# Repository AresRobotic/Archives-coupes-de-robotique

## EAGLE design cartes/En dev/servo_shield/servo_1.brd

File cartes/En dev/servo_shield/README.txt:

* Vérifier connecteur AX-12
Attendre de réussir à faire fonctionner les AX12 pour l'envoyer

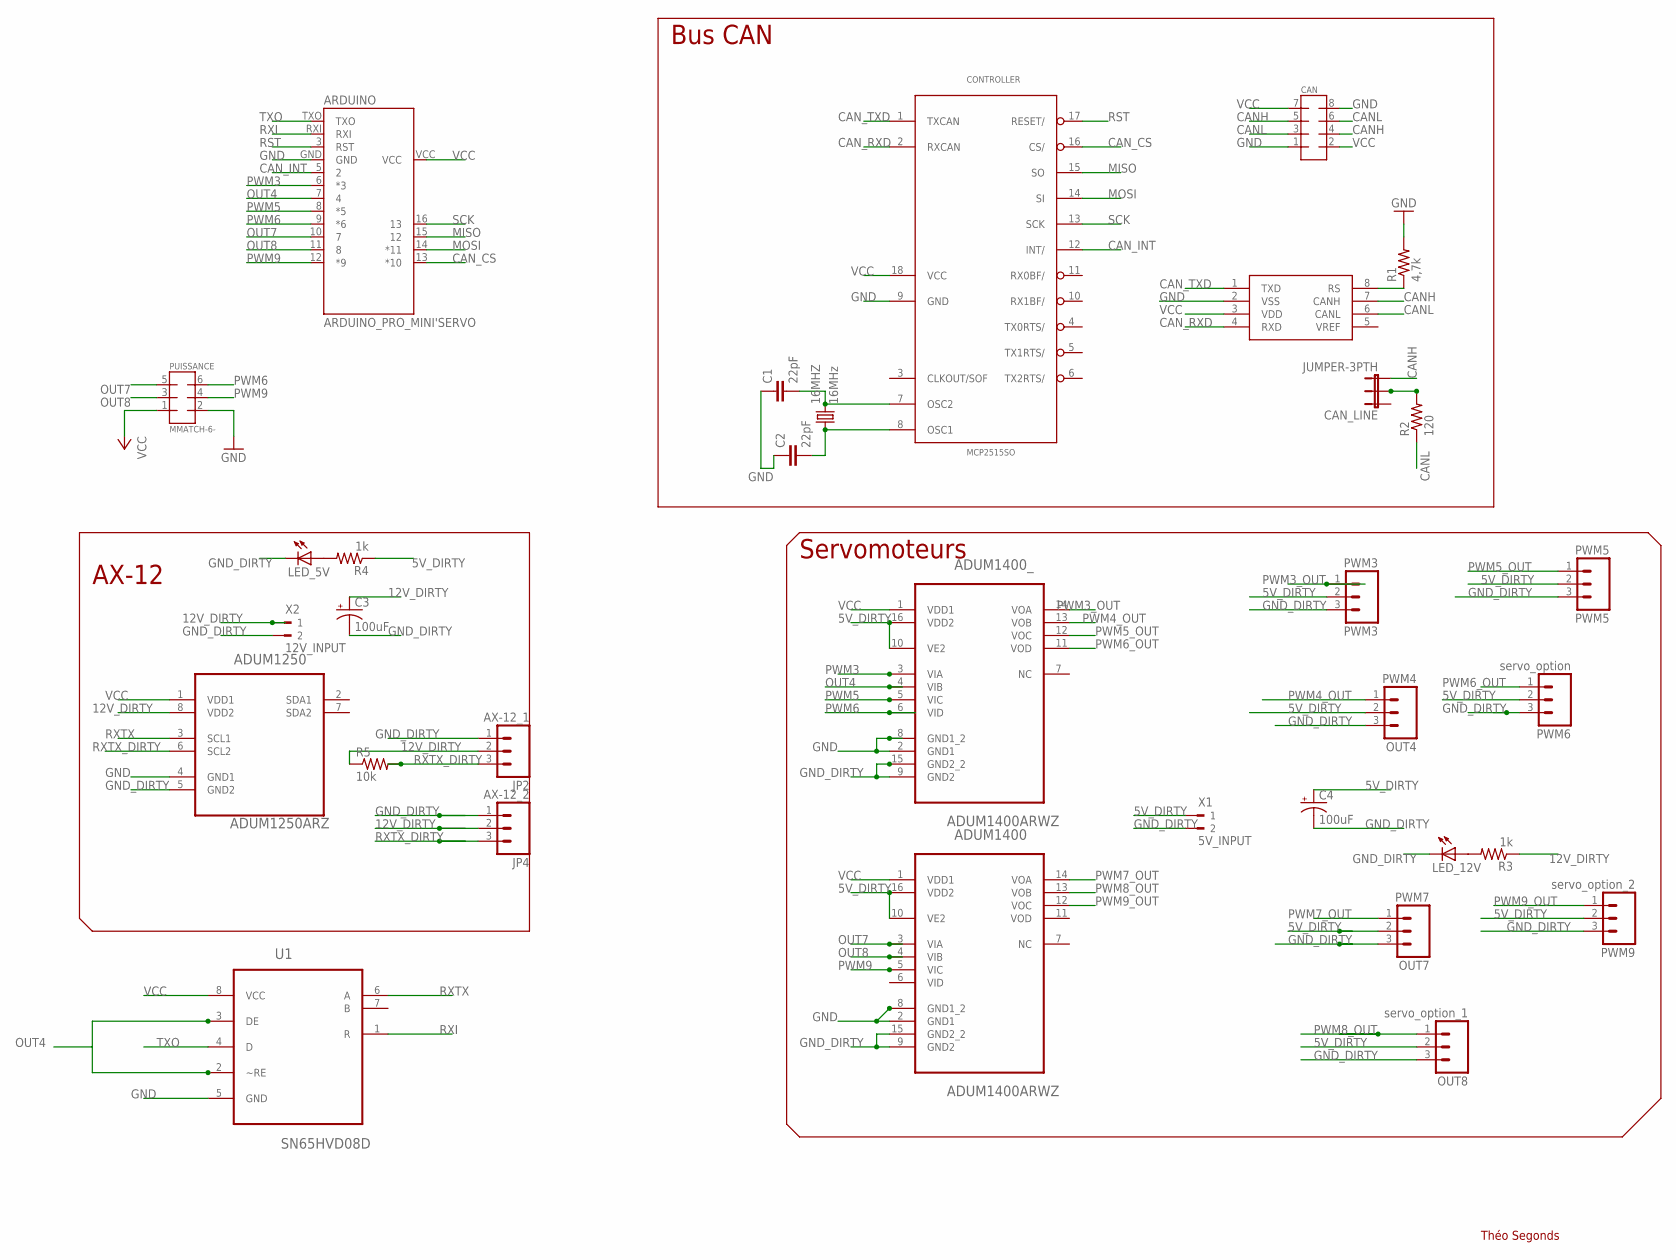
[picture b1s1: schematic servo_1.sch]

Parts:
16MHZ: 16MHz; HC49/S; MPN HC49SM-3.6864-30-50-60-16-ATF
ADUM1250: ADUM1250ARZ; SOIC127P600X175-8N
ADUM1400, ADUM1400_: ADUM1400ARWZ; SOIC127P1032X265-16N
ARDUINO: ARDUINO_PRO_MINI'SERVO; ARDUINO_PRO_MINI
C1, C2: 22pF; 0805; MPN 08055A220JAT2A
C3, C4: 100uF; CPOL-RADIAL-100UF-25V; MPN 100TXW100MEFC8X30
CAN: MMATCH-8-PTH; AMP-215079-8
CAN_LINE: JUMPER-3PTH; 1X03
CONTROLLER: MCP2515SO; SO18L
JP2: AX-12_1; MOLEX-1X3
JP4: AX-12_2; MOLEX-1X3
LED_5V, LED_12V: LEDCHIPLED_0805; CHIPLED_0805
OUT4: PWM4; 1X03
OUT7: PWM7; 1X03
OUT8: servo_option_1; 1X03
PUISSANCE: MMATCH-6-; AMP-215079-6
PWM3: PWM3; 1X03
PWM5: PWM5; 1X03
PWM6: servo_option; 1X03
PWM9: servo_option_2; 1X03
R1: 4,7k; 0805
R2: 120; 0805
R3, R4: 1k; 0805
R5: 10k; 0805
TRANSCEIVER: MCP2551; SO08; MPN MCP2551-I/SN...
U1: SN65HVD08D; SOIC127P600X175-8N
X1: 5V_INPUT; 90-2
X2: 12V_INPUT; 90-2

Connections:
5V_DIRTY: ADUM1400.10 (VE2), ADUM1400.16 (VDD2), ADUM1400_.10 (VE2), ADUM1400_.16 (VDD2), C4.1 (+), OUT4.2, OUT7.2, OUT8.2, PWM3.2, PWM5.2, PWM6.2, PWM9.2, R4.1, X1.1
12V_DIRTY: ADUM1250.8 (VDD2), C3.1 (+), JP2.2, JP4.2, R3.1, R5.1, X2.1
CANH: CAN.4, CAN.5, CAN_LINE.3, TRANSCEIVER.7 (CANH)
CANL: CAN.3, CAN.6, R2.1, TRANSCEIVER.6 (CANL)
CAN_CS: ARDUINO.13 (*10), CONTROLLER.16 (CS/)
CAN_INT: ARDUINO.5 (2), CONTROLLER.12 (INT/)
CAN_RXD: CONTROLLER.2 (RXCAN), TRANSCEIVER.4 (RXD)
CAN_TXD: CONTROLLER.1 (TXCAN), TRANSCEIVER.1 (TXD)
GND: ADUM1250.4 (GND1), ADUM1400.2 (GND1), ADUM1400.8 (GND1_2), ADUM1400_.2 (GND1), ADUM1400_.8 (GND1_2), ARDUINO.GND, C1.1, C2.1, CAN.1, CAN.8, CONTROLLER.9 (GND), PUISSANCE.2 (4), R1.2, TRANSCEIVER.2 (VSS), U1.5 (GND)
GND_DIRTY: ADUM1250.5 (GND2), ADUM1400.9 (GND2), ADUM1400.15 (GND2_2), ADUM1400_.9 (GND2), ADUM1400_.15 (GND2_2), C3.2 (-), C4.2 (-), JP2.1, JP4.1, LED_5V.C, LED_12V.C, OUT4.3, OUT7.3, OUT8.3, PWM3.3, PWM5.3, PWM6.3, PWM9.3, X1.2, X2.2
MISO: ARDUINO.15 (12), CONTROLLER.15 (SO)
MOSI: ARDUINO.14 (*11), CONTROLLER.14 (SI)
unnamed: 16MHZ.2, C1.2, CONTROLLER.7 (OSC2)
unnamed: 16MHZ.1, C2.2, CONTROLLER.8 (OSC1)
unnamed: LED_12V.A, R3.2
unnamed: R1.1, TRANSCEIVER.8 (RS)
unnamed: LED_5V.A, R4.2
unnamed: CAN_LINE.2, R2.2
OUT4: ADUM1400_.4 (VIB), ARDUINO.7 (4), U1.2 (~RE), U1.3 (DE)
OUT7: ADUM1400.3 (VIA), ARDUINO.10 (7), PUISSANCE.5 (7)
OUT8: ADUM1400.4 (VIB), ARDUINO.11 (8), PUISSANCE.3 (5)
PWM3: ADUM1400_.3 (VIA), ARDUINO.6 (*3)
PWM3_OUT: ADUM1400_.14 (VOA), PWM3.1
PWM4_OUT: ADUM1400_.13 (VOB), OUT4.1
PWM5: ADUM1400_.5 (VIC), ARDUINO.8 (*5)
PWM5_OUT: ADUM1400_.12 (VOC), PWM5.1
PWM6: ADUM1400_.6 (VID), ARDUINO.9 (*6), PUISSANCE.6 (8)
PWM6_OUT: ADUM1400_.11 (VOD), PWM6.1
PWM7_OUT: ADUM1400.14 (VOA), OUT7.1
PWM8_OUT: ADUM1400.13 (VOB), OUT8.1
PWM9: ADUM1400.5 (VIC), ARDUINO.12 (*9), PUISSANCE.4 (6)
PWM9_OUT: ADUM1400.12 (VOC), PWM9.1
RST: ARDUINO.3 (RST), CONTROLLER.17 (RESET/)
RXI: ARDUINO.RXI, U1.1 (R)
RXTX: ADUM1250.3 (SCL1), U1.6 (A)
RXTX_DIRTY: ADUM1250.6 (SCL2), JP2.3, JP4.3, R5.2
SCK: ARDUINO.16 (13), CONTROLLER.13 (SCK)
TXO: ARDUINO.TXO, U1.4 (D)
VCC: ADUM1250.1 (VDD1), ADUM1400.1 (VDD1), ADUM1400_.1 (VDD1), ARDUINO.VCC, CAN.2, CAN.7, CONTROLLER.18 (VCC), PUISSANCE.1 (3), TRANSCEIVER.3 (VDD), U1.8 (VCC)

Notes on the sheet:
Bus CAN
AX-12
Servomoteurs
Théo Segonds

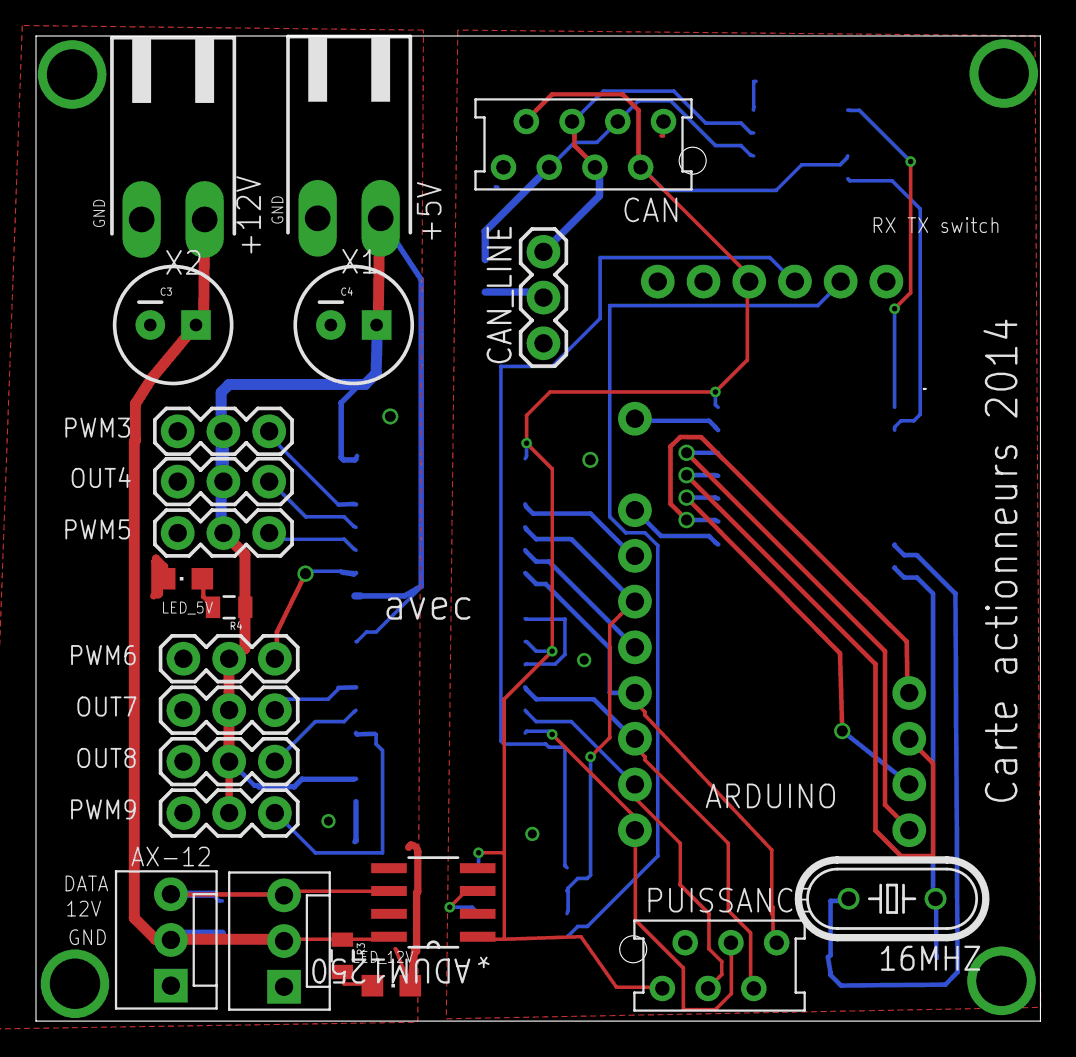
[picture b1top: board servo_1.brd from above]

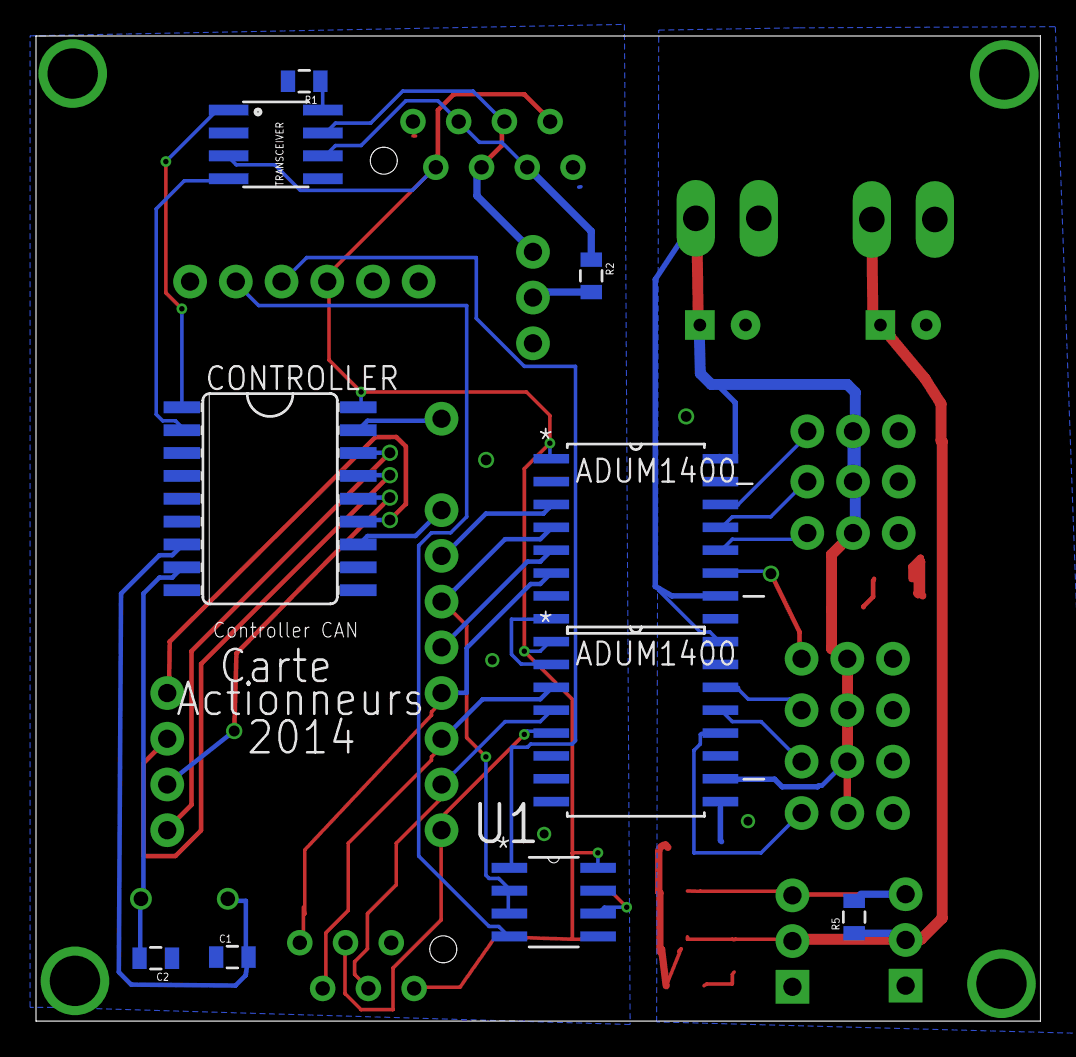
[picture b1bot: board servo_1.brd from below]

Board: 2 copper layers, 55.8 x 54.7 mm, 33 parts (10 on the bottom side), 39 nets.

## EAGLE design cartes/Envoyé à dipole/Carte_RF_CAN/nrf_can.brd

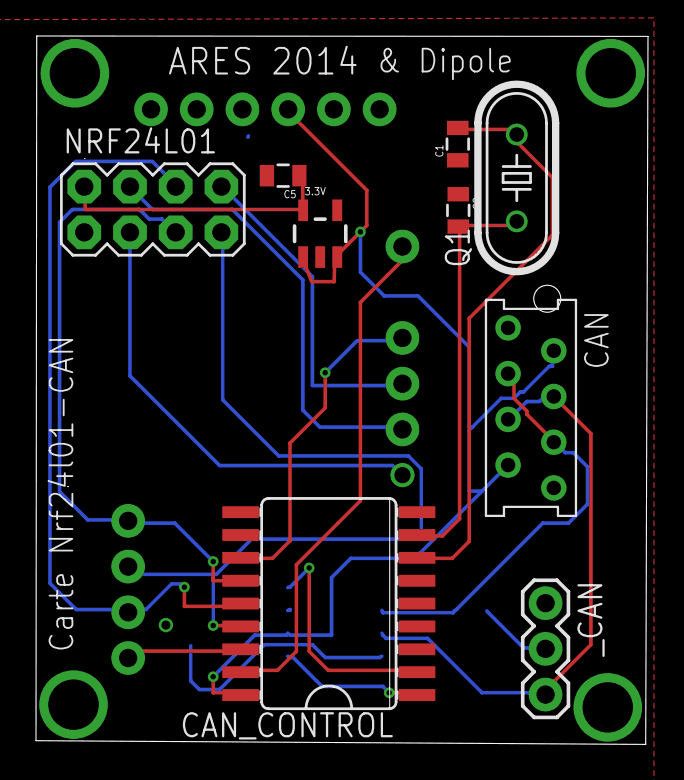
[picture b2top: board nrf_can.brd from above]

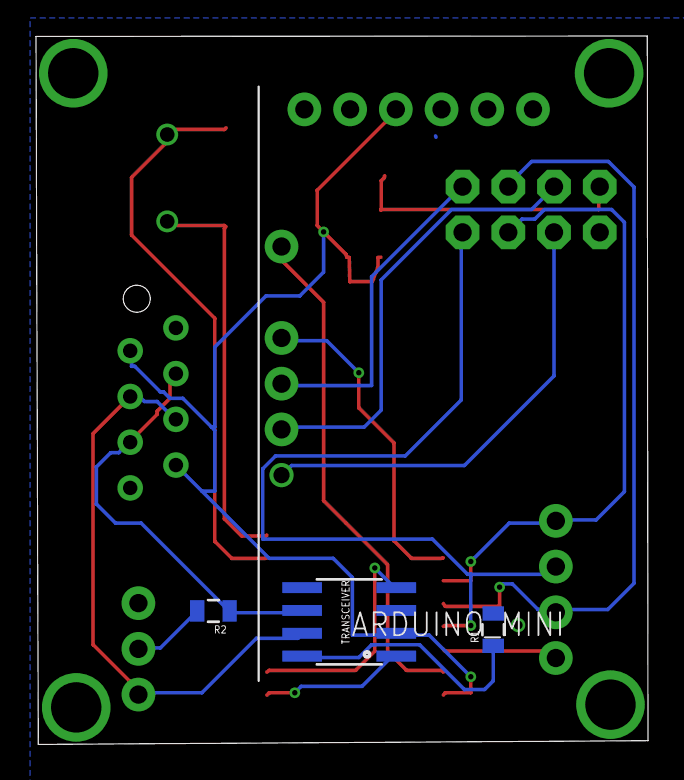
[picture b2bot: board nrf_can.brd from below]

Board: 2 copper layers, 34.0 x 39.4 mm, 13 parts (4 on the bottom side), 20 nets.

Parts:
3.3V: 3.3V/150mA; SOT23-5
ARDUINO_MINI: ARDUINO_PRO_MINI
C1, C2: 22pF; 0805
C5: 1uF; 0805
CAN: micromatch8p; AMP-215079-8
CAN_CONTROL: MCP2515SO; SO18L
NRF24L01: M04X2; 2X4
Q1: 16MHz; HC49/S
R1: 4,7k; 0805
R2: 120; 0805
TRANSCEIVER: MCP2551; SO08
_CAN: JUMPER-3PTH; 1X03

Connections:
3.3V: 3.3V.5, C5.1, NRF24L01.2
CANH: CAN.4, CAN.5, TRANSCEIVER.7, _CAN.3
CANL: CAN.3, CAN.6, R2.1, TRANSCEIVER.6
CAN_CS: ARDUINO_MINI.13, CAN_CONTROL.16
CAN_INT: ARDUINO_MINI.5, CAN_CONTROL.12
CAN_RXD: CAN_CONTROL.2, TRANSCEIVER.4
CAN_TXD: CAN_CONTROL.1, TRANSCEIVER.1
GND: 3.3V.2, ARDUINO_MINI.GND, C1.1, C2.1, C5.2, CAN.1, CAN.8, CAN_CONTROL.9, NRF24L01.1, R1.2, TRANSCEIVER.3
MISO: ARDUINO_MINI.15, CAN_CONTROL.15, NRF24L01.7
MOSI: ARDUINO_MINI.14, CAN_CONTROL.14, NRF24L01.6
unnamed: C1.2, CAN_CONTROL.7, Q1.2
unnamed: C2.2, CAN_CONTROL.8, Q1.1
unnamed: R1.1, TRANSCEIVER.8
unnamed: R2.2, _CAN.2
NRF_CE: ARDUINO_MINI.8, NRF24L01.3
NRF_CSN: ARDUINO_MINI.7, NRF24L01.4
NRF_IRQ: ARDUINO_MINI.6, NRF24L01.8
RST: ARDUINO_MINI.3, CAN_CONTROL.17
SCK: ARDUINO_MINI.16, CAN_CONTROL.13, NRF24L01.5
VCC: 3.3V.1, 3.3V.3, ARDUINO_MINI.VCC, CAN.2, CAN.7, CAN_CONTROL.18, TRANSCEIVER.2

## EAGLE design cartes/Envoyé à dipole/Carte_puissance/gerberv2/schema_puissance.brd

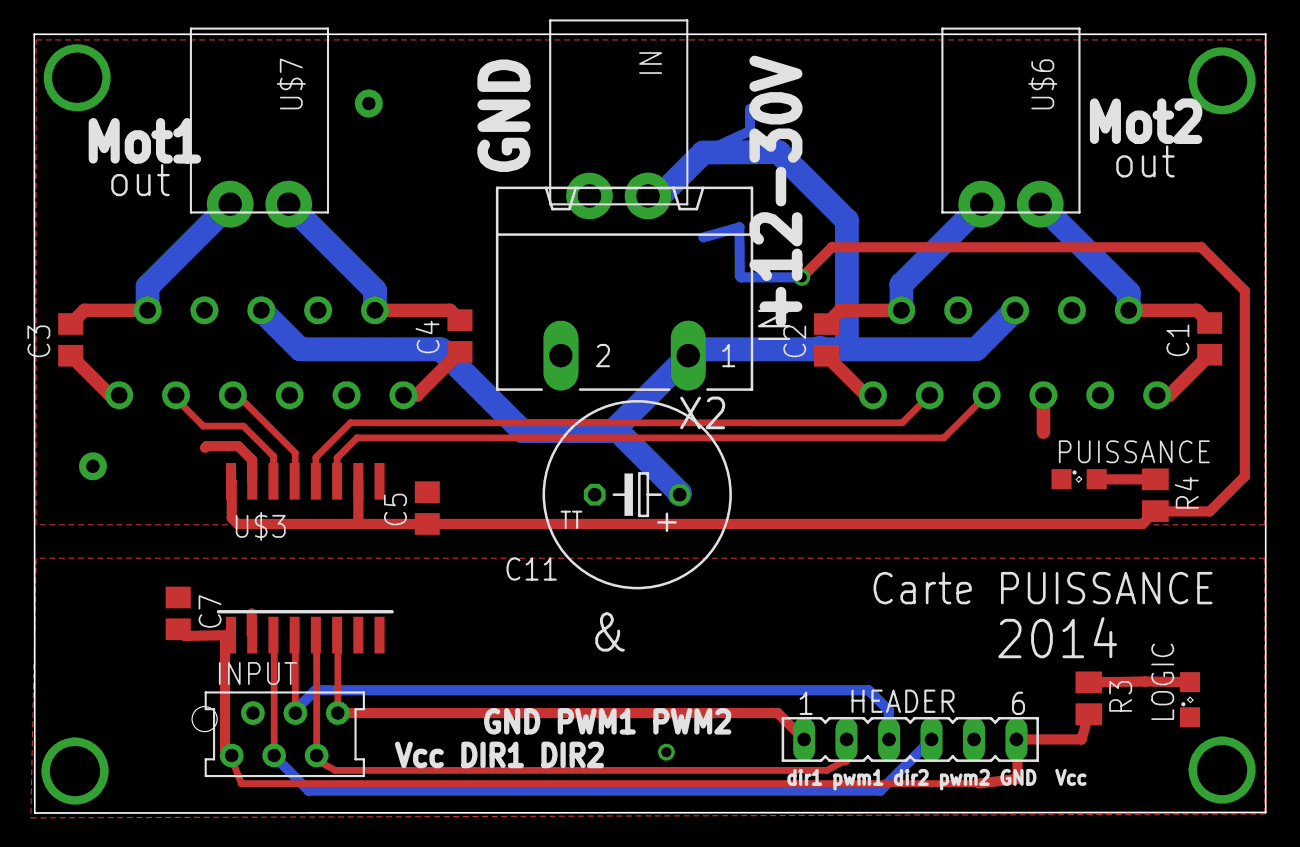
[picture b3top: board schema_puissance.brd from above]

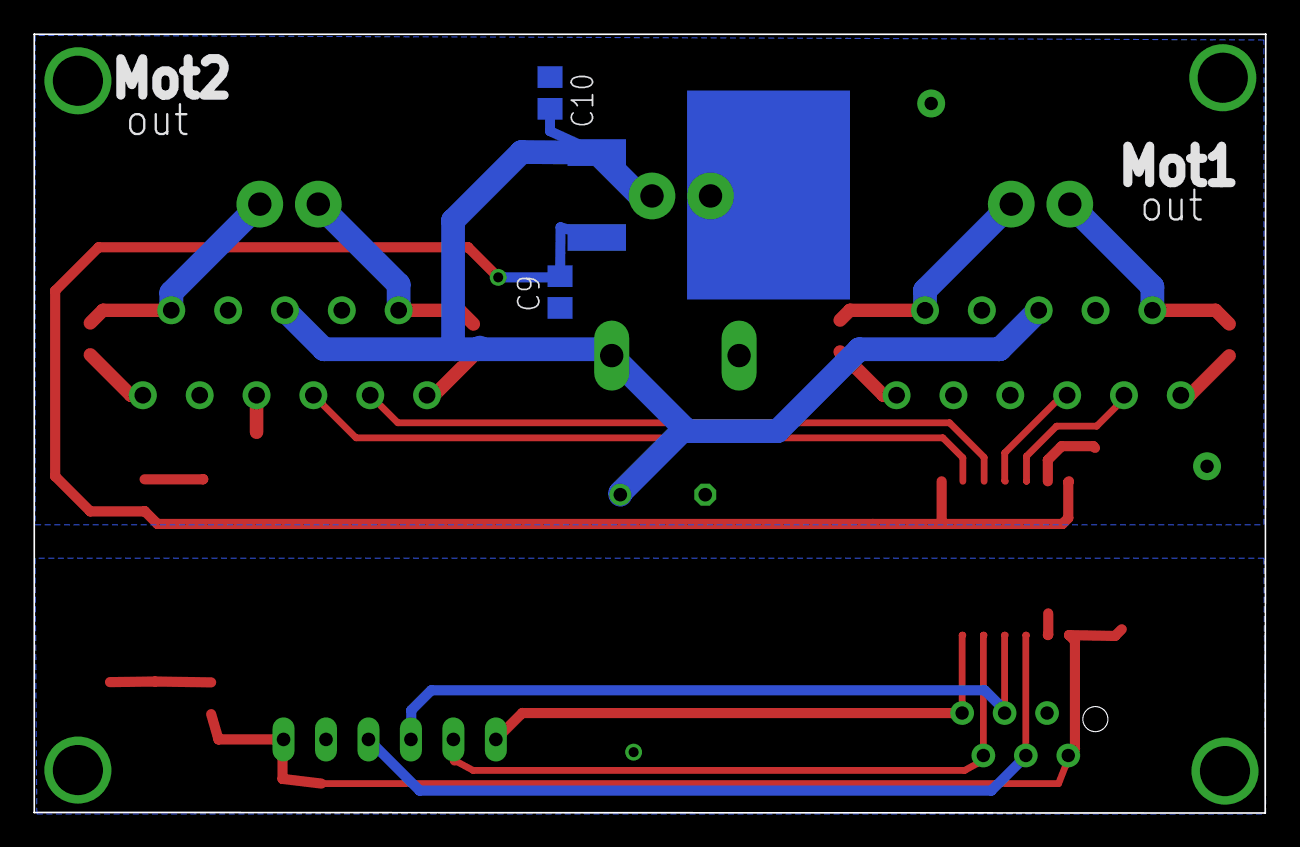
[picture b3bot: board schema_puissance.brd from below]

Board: 2 copper layers, 73.7 x 46.6 mm, 23 parts (3 on the bottom side), 23 nets.

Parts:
C1, C2, C3, C4: 10nF; C0805
C5, C7, C9: 100nF; C0805
C10: 330nF; C0805
C11: 2200u; TT5D11
HEADER: FE06
IN: SL-3.5-2-90G
INPUT: MMATCH-6-; AMP-215079-6
LOGIC: SML0805
PUISSANCE: SML0805
R3, R4: 1k; M0805
U$1, U$2: LMD18200
U$3: ADUM1400S; SO-16W
U$5: L7805TO263; DPAK
U$6, U$7: SL-3.5-2-90G
X2: GMSTBA2

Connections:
+5V: C5.1, C9.2, R4.2, U$3.10, U$3.16, U$5.3
+12V: C10.2, C11.+, IN.2, U$1.6, U$2.6, U$5.2, X2.1
C_DIR1: HEADER.4, INPUT.3, U$3.3
C_DIR2: HEADER.2, INPUT.5, U$3.5
C_PWM1: HEADER.3, INPUT.4, U$3.4
C_PWM2: HEADER.1, INPUT.6, U$3.6
DIR1: U$1.3, U$3.14
DIR2: U$2.3, U$3.12
GND: C7.1, HEADER.5, INPUT.2, LOGIC.C, U$3.2, U$3.8
GNDA: C5.2, C9.1, C10.1, C11.-, IN.1, PUISSANCE.C, U$1.4, U$1.7, U$2.4, U$2.7, U$3.9, U$3.15, U$5.1, X2.2
unnamed: C1.1, U$2.11
unnamed: PUISSANCE.A, R4.1
unnamed: C2.1, U$2.1
unnamed: LOGIC.A, R3.1
unnamed: C3.1, U$1.1
unnamed: C4.1, U$1.11
POLE_1_MOT1: C3.2, U$1.2, U$7.1
POLE_1_MOT2: C2.2, U$2.2, U$6.1
POLE_2_MOT1: C4.2, U$1.10, U$7.2
POLE_2_MOT2: C1.2, U$2.10, U$6.2
PWM1: U$1.5, U$3.13
PWM2: U$2.5, U$3.11
VCC: C7.2, HEADER.6, INPUT.1, R3.2, U$3.1

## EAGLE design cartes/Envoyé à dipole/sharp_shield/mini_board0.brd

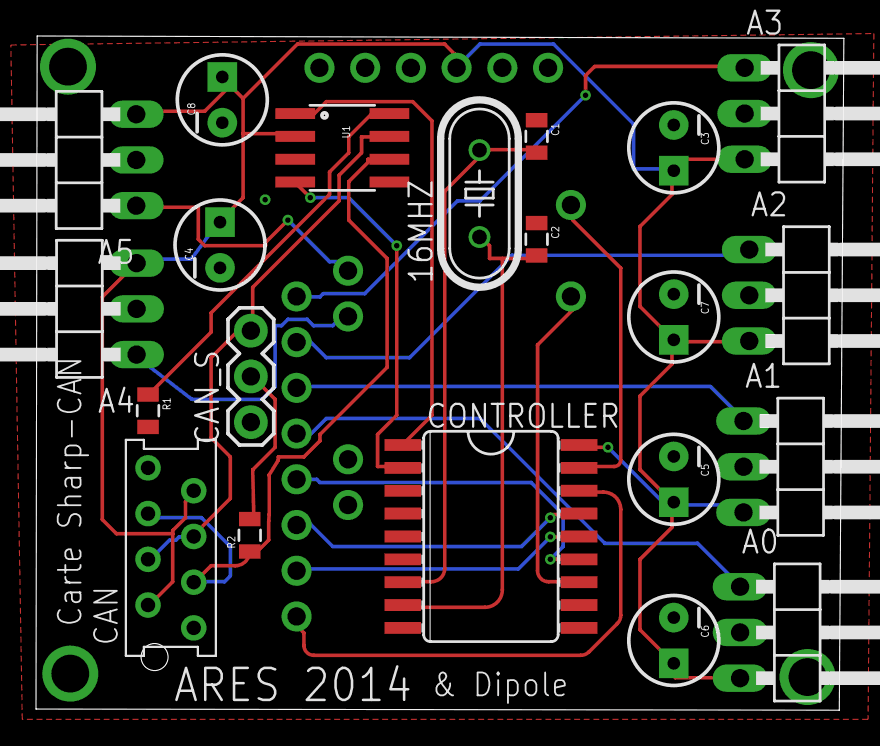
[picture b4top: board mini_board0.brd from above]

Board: 2 copper layers, 44.9 x 37.5 mm, 22 parts (1 on the bottom side), 22 nets.

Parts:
16MHZ: 16MHz; HC49/S
A0, A1, A2, A3, A4, A5: 1X03/90
ARDUINO: ARDUINO_PRO_MINI
C1, C2: 22pF; 0805
C3, C4, C5, C6, C7, C8: CPOL-RADIAL-10UF-25V
CAN: AMP-215079-8
CAN_S: JUMPER-3PTH; 1X03
CONTROLLER: MCP2515SO; SO18L
R1: 4,7k; 0805
R2: 120; 0805
U1: MCP2551; SO08

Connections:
A0: A0.1, ARDUINO.17
A1: A1.1, ARDUINO.18
A2: A2.1, ARDUINO.19
A3: A3.1, ARDUINO.20
A4: A4.1, ARDUINO.A4
A5: A5.1, ARDUINO.A5
CANH: CAN.4, CAN.5, CAN_S.3, U1.7
CANL: CAN.3, CAN.6, R2.1, U1.6
CAN_CS: ARDUINO.13, CONTROLLER.16
CAN_INT: ARDUINO.5, CONTROLLER.12
CAN_RXD: CONTROLLER.2, U1.4
CAN_TXD: CONTROLLER.1, U1.1
GND: A0.2, A1.2, A2.2, A3.2, A4.2, A5.2, ARDUINO.GND, C1.1, C2.1, C3.2, C4.2, C5.2, C6.2, C7.2, C8.2, CAN.1, CAN.8, CONTROLLER.9, R1.2, U1.3
MISO: ARDUINO.15, CONTROLLER.15
MOSI: ARDUINO.14, CONTROLLER.14
unnamed: 16MHZ.2, C1.2, CONTROLLER.7
unnamed: 16MHZ.1, C2.2, CONTROLLER.8
unnamed: R1.1, U1.8
unnamed: CAN_S.2, R2.2
RST: ARDUINO.3, CONTROLLER.17
SCK: ARDUINO.16, CONTROLLER.13
VCC: A0.3, A1.3, A2.3, A3.3, A4.3, A5.3, ARDUINO.VCC, C3.1, C4.1, C5.1, C6.1, C7.1, C8.1, CAN.2, CAN.7, CONTROLLER.18, U1.2

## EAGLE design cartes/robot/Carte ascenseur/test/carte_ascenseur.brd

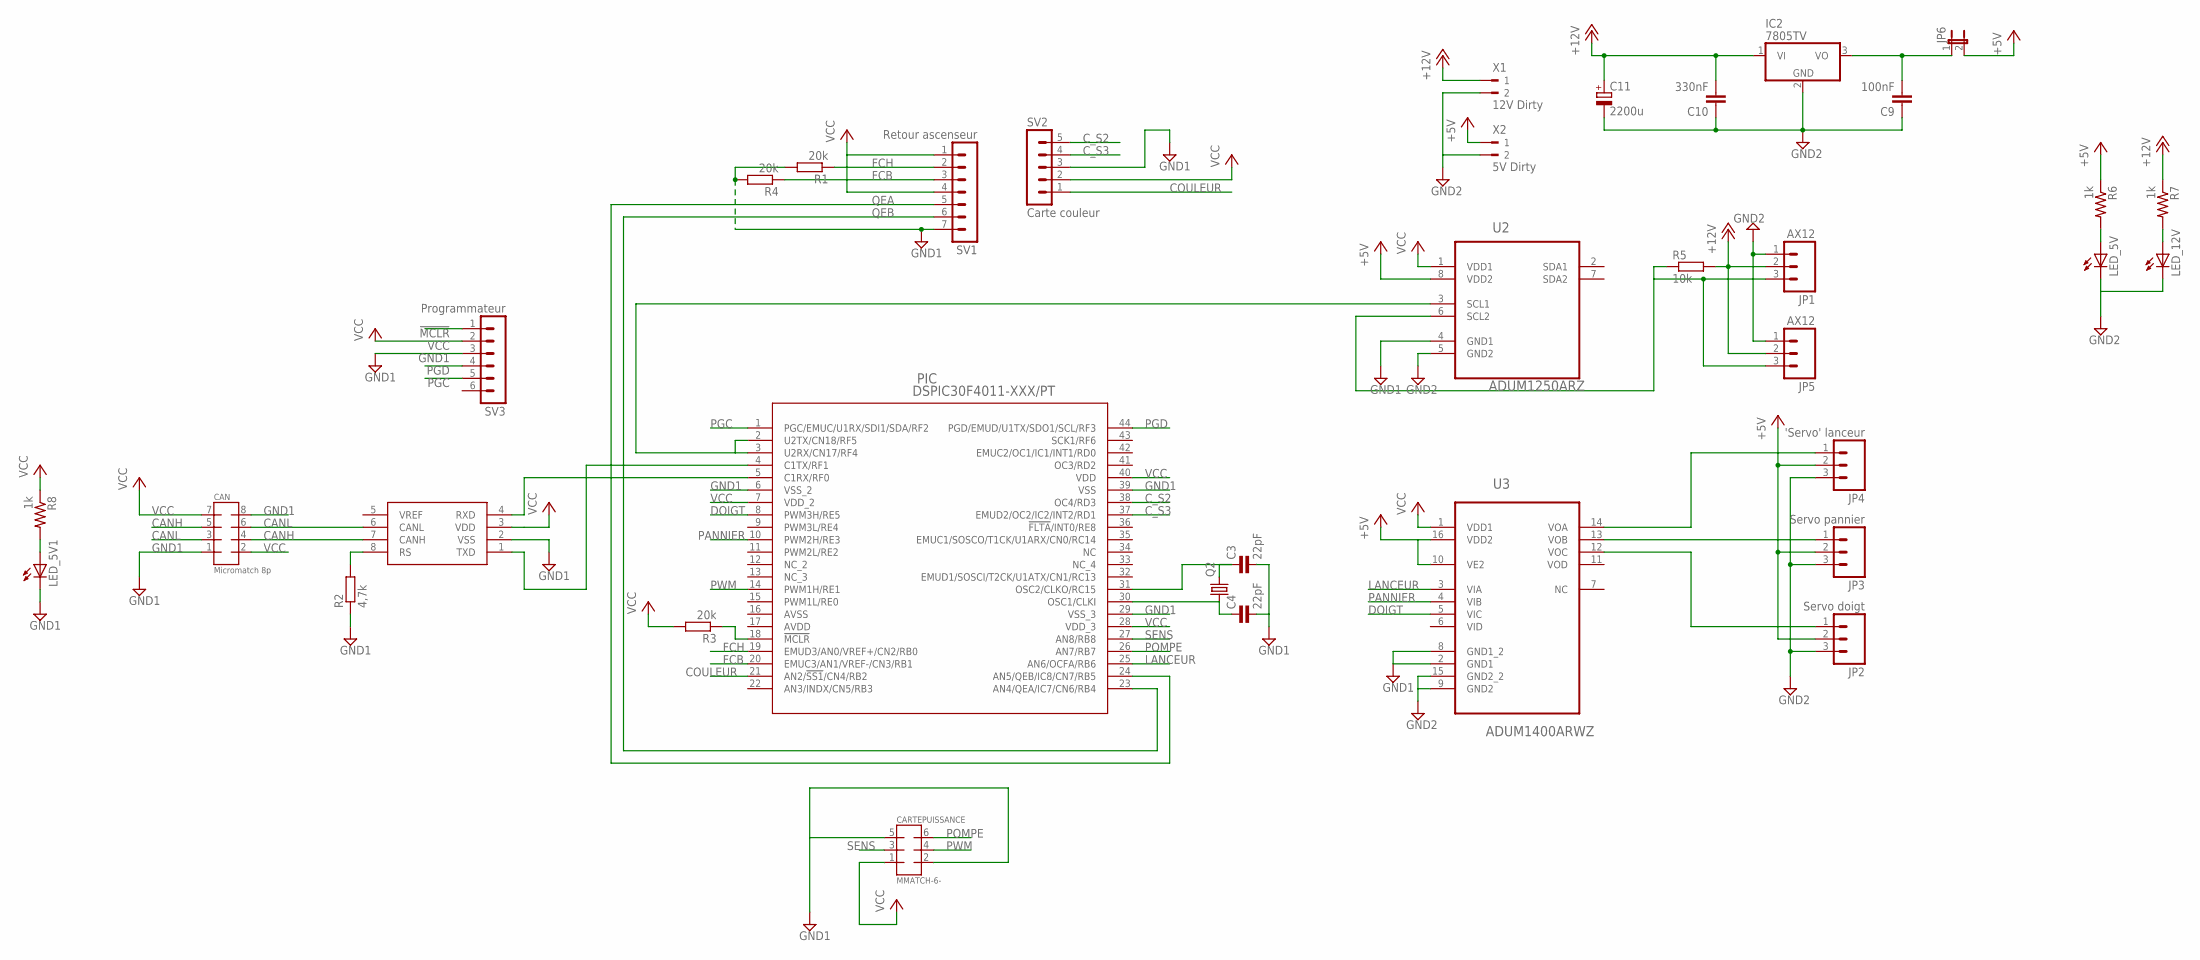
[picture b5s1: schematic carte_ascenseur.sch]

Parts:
C3, C4: 22pF; 0805
C9: 100nF; C0805
C10: 330nF; C0805
C11: 2200u; TT5D11
CAN: Micromatch 8p; AMP-215079-8
CARTEPUISSANCE: MMATCH-6-; AMP-215079-6
IC2: 7805TV; TO220V
JP1, JP5: AX12; MOLEX-1X3
JP2: Servo doigt; 1X03
JP3: Servo pannier; 1X03
JP4: 'Servo' lanceur; 1X03
JP6: JP1E; JP1
LED_5V, LED_5V1, LED_12V: LEDCHIPLED_0805; CHIPLED_0805
PIC: DSPIC30F4011-XXX/PT; TQFP44_MC
Q2: CRYSTALHC49S; HC49/S
R1, R3, R4: 20k; M0805
R2: 4,7k; M0805
R5: 10k; M0805
R6, R7, R8: 1k; 0805
SV1: Retour ascenseur; MA07-1
SV2: Carte couleur; MA05-1
SV3: Programmateur; MA06-1
U1: MCP2551; SO08
U2: ADUM1250ARZ; SOIC127P600X175-8N
U3: ADUM1400ARWZ; SOIC127P1032X265-16N
X1: 12V Dirty; 90-2
X2: 5V Dirty; 90-2

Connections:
!MCLR!: PIC.18 (!MCLR!), R3.1, SV3.1
+5V: JP2.2, JP3.2, JP4.2, JP6.2, R6.1, U2.8 (VDD2), U3.10 (VE2), U3.16 (VDD2), X2.1
+12V: C10.2, C11.+, IC2.1 (VI), JP1.2, JP5.2, R5.2, R7.1, X1.1
CANH: CAN.4, CAN.5, U1.7 (CANH)
CANL: CAN.3, CAN.6, U1.6 (CANL)
COULEUR: PIC.21 (AN2/!SS1!/CN4/RB2), SV2.1
C_S2: PIC.38 (OC4/RD3), SV2.5
C_S3: PIC.37 (EMUD2/OC2/IC2/INT2/RD1), SV2.4
DOIGT: PIC.8 (PWM3H/RE5), U3.5 (VIC)
FCB: PIC.20 (EMUC3/AN1/VREF-/CN3/RB1), R4.1, SV1.3
FCH: PIC.19 (EMUD3/AN0/VREF+/CN2/RB0), R1.1, SV1.2
GND1: C3.2, C4.2, CAN.1, CAN.8, CARTEPUISSANCE.2 (4), CARTEPUISSANCE.5 (7), LED_5V1.C, PIC.6 (VSS_2), PIC.29 (VSS_3), PIC.39 (VSS), R1.2, R2.1, R4.2, SV1.7, SV2.3, SV3.3, U1.2 (VSS), U2.4 (GND1), U3.2 (GND1), U3.8 (GND1_2)
GND2: C9.1, C10.1, C11.-, IC2.2 (GND), JP1.1, JP2.3, JP3.3, JP4.3, JP5.1, LED_5V.C, LED_12V.C, U2.5 (GND2), U3.9 (GND2), U3.15 (GND2_2), X1.2, X2.2
LANCEUR: PIC.25 (AN6/OCFA/RB6), U3.3 (VIA)
unnamed: PIC.4 (C1TX/RF1), U1.1 (TXD)
unnamed: LED_5V.A, R6.2
unnamed: PIC.5 (C1RX/RF0), U1.4 (RXD)
unnamed: R2.2, U1.8 (RS)
unnamed: C9.2, IC2.3 (VO), JP6.1
unnamed: PIC.2 (U2TX/CN18/RF5), PIC.3 (U2RX/CN17/RF4), U2.3 (SCL1)
unnamed: JP4.1, U3.14 (VOA)
unnamed: JP3.1, U3.13 (VOB)
unnamed: JP2.1, U3.12 (VOC)
unnamed: LED_12V.A, R7.2
unnamed: LED_5V1.A, R8.2
unnamed: C3.1, PIC.31 (OSC2/CLKO/RC15), Q2.2
unnamed: JP1.3, JP5.3, R5.1, U2.6 (SCL2)
unnamed: C4.1, PIC.30 (OSC1/CLKI), Q2.1
PANNIER: PIC.10 (PWM2H/RE3), U3.4 (VIB)
PGC: PIC.1 (PGC/EMUC/U1RX/SDI1/SDA/RF2), SV3.5
PGD: PIC.44 (PGD/EMUD/U1TX/SDO1/SCL/RF3), SV3.4
POMPE: CARTEPUISSANCE.6 (8), PIC.26 (AN7/RB7)
PWM: CARTEPUISSANCE.4 (6), PIC.14 (PWM1H/RE1)
QEA: PIC.24 (AN5/QEB/IC8/CN7/RB5), SV1.5
QEB: PIC.23 (AN4/QEA/IC7/CN6/RB4), SV1.6
SENS: CARTEPUISSANCE.3 (5), PIC.27 (AN8/RB8)
VCC: CAN.2, CAN.7, CARTEPUISSANCE.1 (3), PIC.7 (VDD_2), PIC.28 (VDD_3), PIC.40 (VDD), R3.2, R8.1, SV1.1, SV1.4, SV2.2, SV3.2, U1.3 (VDD), U2.1 (VDD1), U3.1 (VDD1)

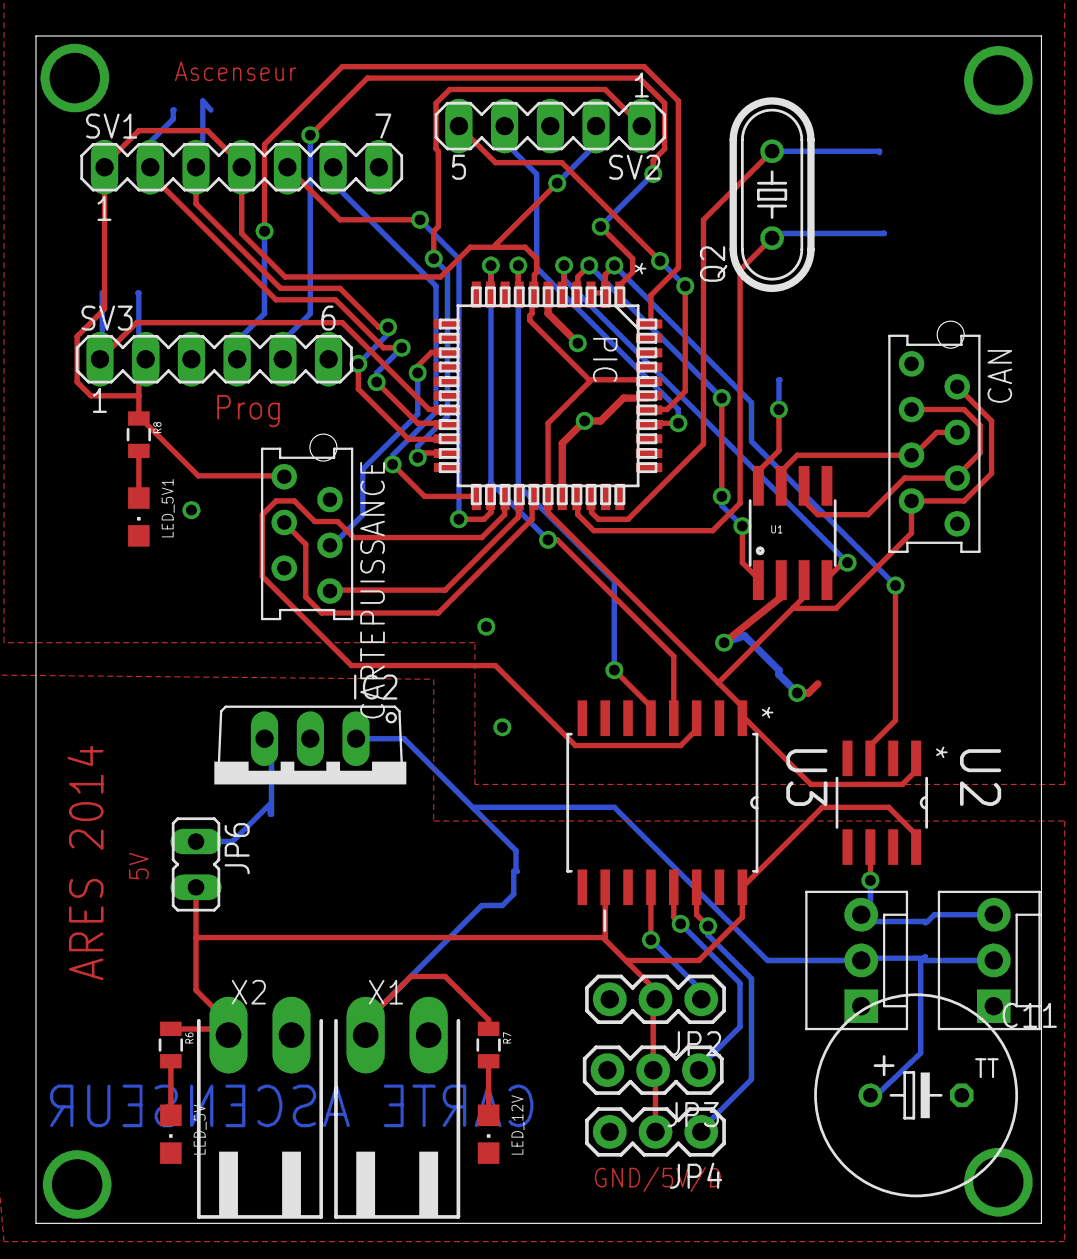
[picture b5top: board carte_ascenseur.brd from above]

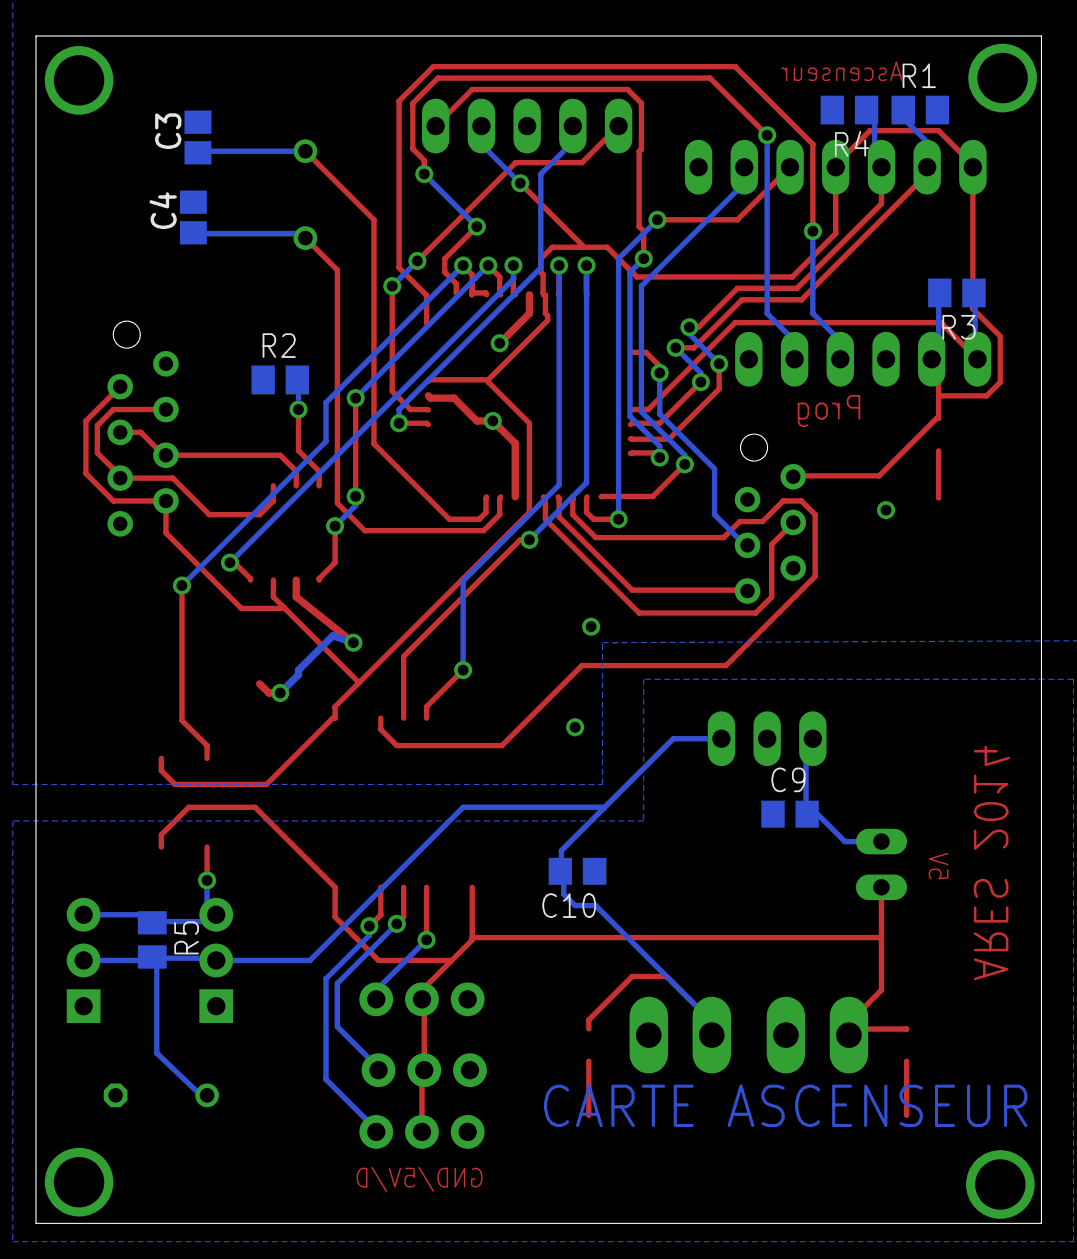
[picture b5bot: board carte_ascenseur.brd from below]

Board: 2 copper layers, 55.9 x 66.0 mm, 35 parts (9 on the bottom side), 37 nets.

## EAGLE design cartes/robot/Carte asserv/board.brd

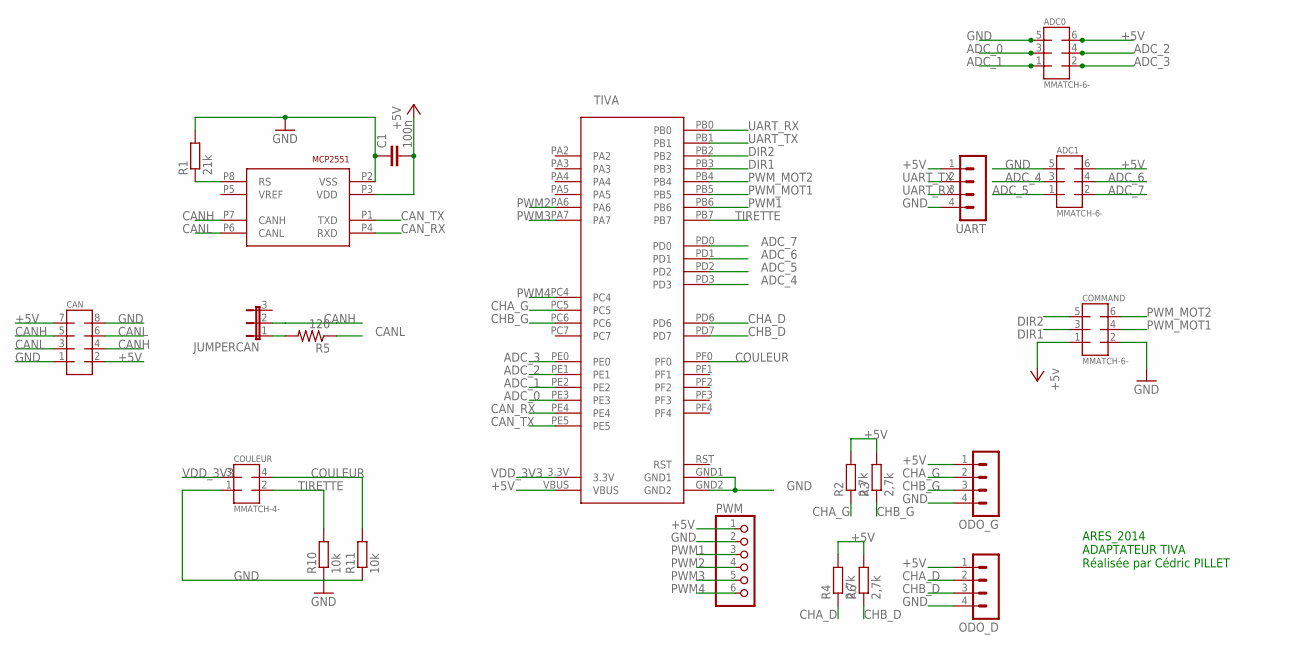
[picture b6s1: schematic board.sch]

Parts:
ADC0, ADC1: MMATCH-6-; AMP-215079-6
C1: 100n; C0805
CAN: MMATCH-8-PTH; AMP-215079-8
COMMAND: MMATCH-6-; AMP-215079-6
COULEUR: MMATCH-4-; AMP-215079-4
JUMPERCAN: JP2W
ODO_D: MA04-1
ODO_G: MA04-1
PWM: PINHD-1X6/90; 1X06/90
R1: 21k; R0805
R2, R3, R4, R6: 2,7k; R0805
R5: 120; M0805
R10, R11: 10k; R0805
TIVA: STELLARIS-LAUNCHPADSTELLARIS-LAUNCHPAD; LAUNCHPAD-XL
U$1: MCP2551; SOIC_8
UART: MA04-1

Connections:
+5V: ADC0.6 (8), ADC1.6 (8), C1.2, CAN.2, CAN.7, COMMAND.1 (3), ODO_D.1, ODO_G.1, PWM.1, R2.2, R3.2, R4.2, R6.2, TIVA.VBUS, U$1.P3 (VDD), UART.1
ADC_0: ADC0.3 (5), TIVA.PE3
ADC_1: ADC0.1 (3), TIVA.PE2
ADC_2: ADC0.4 (6), TIVA.PE1
ADC_3: ADC0.2 (4), TIVA.PE0
ADC_4: ADC1.3 (5), TIVA.PD3
ADC_5: ADC1.1 (3), TIVA.PD2
ADC_6: ADC1.4 (6), TIVA.PD1
ADC_7: ADC1.2 (4), TIVA.PD0
CANH: CAN.4, CAN.5, JUMPERCAN.2, U$1.P7 (CANH)
CANL: CAN.3, CAN.6, R5.1, U$1.P6 (CANL)
CAN_RX: TIVA.PE4, U$1.P4 (RXD)
CAN_TX: TIVA.PE5, U$1.P1 (TXD)
CHA_D: ODO_D.2, R4.1, TIVA.PD6
CHA_G: ODO_G.2, R2.1, TIVA.PC5
CHB_D: ODO_D.3, R6.1, TIVA.PD7
CHB_G: ODO_G.3, R3.1, TIVA.PC6
COULEUR: COULEUR.4 (8), R11.2, TIVA.PF0
DIR1: COMMAND.3 (5), TIVA.PB3
DIR2: COMMAND.5 (7), TIVA.PB2
GND: ADC0.5 (7), ADC1.5 (7), C1.1, CAN.1, CAN.8, COMMAND.2 (4), COULEUR.1 (5), ODO_D.4, ODO_G.4, PWM.2, R1.2, R10.1, R11.1, TIVA.GND1, TIVA.GND2, U$1.P2 (VSS), UART.4
unnamed: R1.1, U$1.P8 (RS)
unnamed: JUMPERCAN.1, R5.2
PWM1: PWM.3, TIVA.PB6
PWM2: PWM.4, TIVA.PA6
PWM3: PWM.5, TIVA.PA7
PWM4: PWM.6, TIVA.PC4
PWM_MOT1: COMMAND.4 (6), TIVA.PB5
PWM_MOT2: COMMAND.6 (8), TIVA.PB4
RST: TIVA.RST
TIRETTE: COULEUR.2 (6), R10.2, TIVA.PB7
UART_RX: TIVA.PB0, UART.3
UART_TX: TIVA.PB1, UART.2
VDD_3V3: COULEUR.3 (7), TIVA.3.3V

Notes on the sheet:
ARES_2014 ADAPTATEUR TIVA Réalisée par Cédric PILLET

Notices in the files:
parts and their libraries:
SparkFun-DigitalIC: Licensing: CC v3.0 Share-Alike You are welcome to use this library for commercial purposes.
